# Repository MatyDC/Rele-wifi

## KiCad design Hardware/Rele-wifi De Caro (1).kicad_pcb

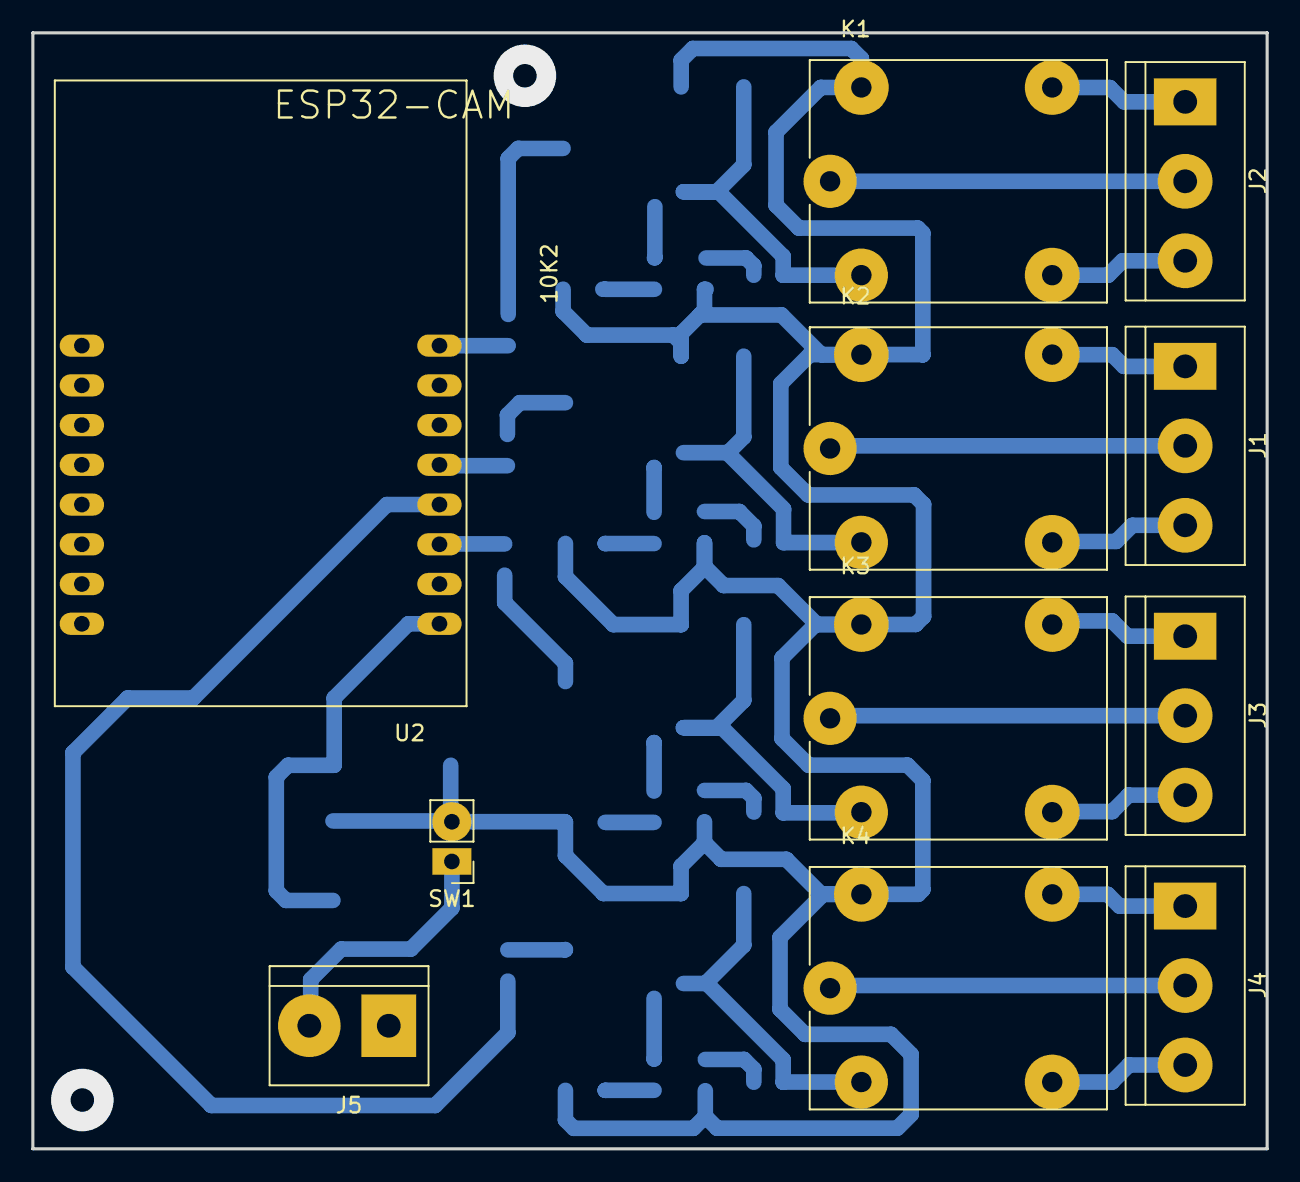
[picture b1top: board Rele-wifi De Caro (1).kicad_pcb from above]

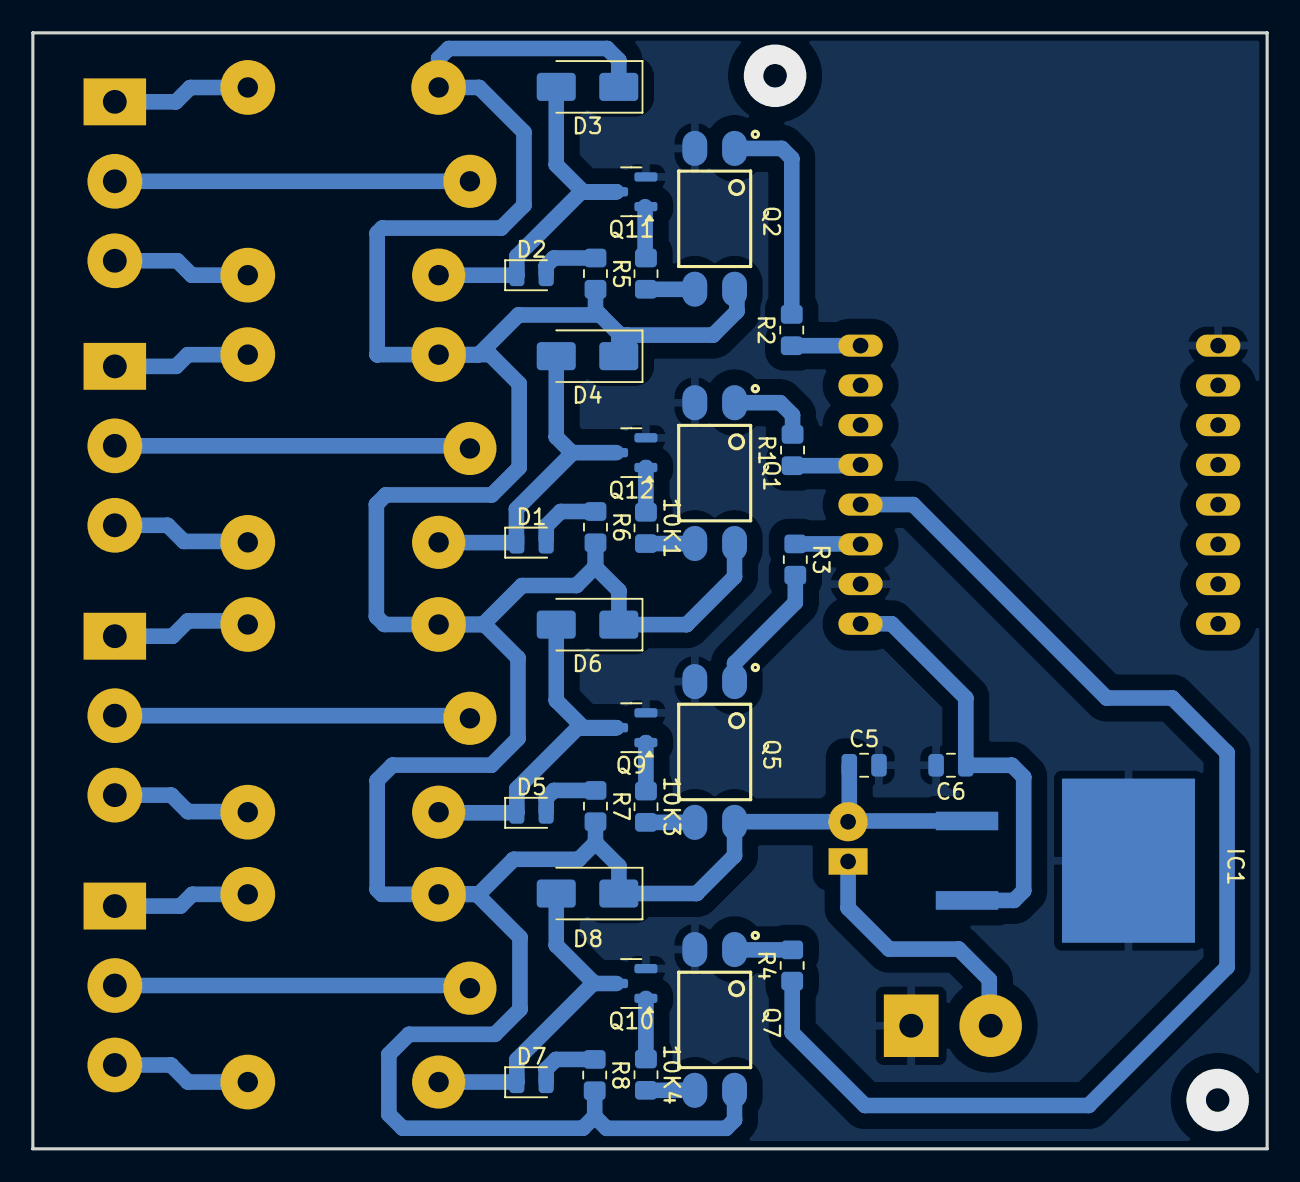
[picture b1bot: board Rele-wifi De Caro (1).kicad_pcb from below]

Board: 2 copper layers, 78.9 x 71.3 mm, 42 parts (31 on the bottom side), 40 nets.

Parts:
10K1, 10K2, 10K3, 10K4: R; R_0805_2012Metric_Pad1.20x1.40mm_HandSolder
C5, C6: 0.1uF; C_0805_2012Metric
D1, D2, D5, D7: LED; LED_0805_2012Metric
D3, D4, D6, D8: D; D_SMA
IC1: MC7805CD2TG
J1, J2, J3, J4: Screw_Terminal_01x03; TerminalBlock_bornier-3_P5.08mm
J5: Screw_Terminal_01x02; TerminalBlock_bornier-2_P5.08mm
K1, K2, K3, K4: PR13-5V-450-1C; RELAY_PR13-5V-450-1C
Q1, Q2, Q5, Q7: PC817-B; SOT254P1025X400-4N
Q9, Q10, Q11, Q12: BC847; SOT-23
R1, R2, R3, R4: 220; R_0805_2012Metric_Pad1.20x1.40mm_HandSolder
R5, R6, R7, R8: 680; R_0805_2012Metric_Pad1.20x1.40mm_HandSolder
SW1: SW_DPST_x2; PinHeader_1x02_P2.54mm_Vertical
U2: ESP32-CAM

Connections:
GND: C5.2, C6.2, IC1.P$1 (GND), J5.1, Q1.2, Q2.2, Q5.2, Q7.2, Q9.2 (E), Q10.2 (E), Q11.2 (E), Q12.2 (E), U2.P$2 (GND), U2.P$9 (.GND)
GPIO 4: R2.1, U2.P$8 (IO4)
GPIO 12: R3.1, U2.P$3 (IO12)
GPIO 13: R4.1, U2.P$4 (IO13)
GPIO 15: R1.1, U2.P$5 (IO15)
unnamed: 10K1.2, Q1.3
unnamed: 10K2.2, Q2.3
unnamed: 10K3.2, Q5.3
unnamed: 10K4.2, Q7.3
unnamed: D1.2 (A), R6.1
unnamed: D1.1 (K), D4.2 (A), K2.A2, Q12.3 (C)
unnamed: D2.2 (A), R5.1
unnamed: D2.1 (K), D3.2 (A), K1.A2, Q11.3 (C)
unnamed: D5.2 (A), R7.1
unnamed: D5.1 (K), D6.2 (A), K3.A2, Q9.3 (C)
unnamed: D7.2 (A), R8.1
unnamed: D7.1 (K), D8.2 (A), K4.A2, Q10.3 (C)
unnamed: C6.1, IC1.P$3 (VOUT), U2.P$1 (5V)
unnamed: J1.1, K2.NC
unnamed: J1.2, K2.COM
unnamed: J1.3, K2.NO
unnamed: J2.1, K1.NC
unnamed: J2.2, K1.COM
unnamed: J2.3, K1.NO
unnamed: J3.1, K3.NC
unnamed: J3.2, K3.COM
unnamed: J3.3, K3.NO
unnamed: J4.1, K4.NC
unnamed: J4.2, K4.COM
unnamed: J4.3, K4.NO
unnamed: J5.2, SW1.1 (A)
unnamed: Q1.1, R1.2
unnamed: Q2.1, R2.2
unnamed: Q5.1, R3.2
unnamed: Q7.1, R4.2
unnamed: 10K3.1, Q9.1 (B)
unnamed: 10K4.1, Q10.1 (B)
unnamed: 10K2.1, Q11.1 (B)
unnamed: 10K1.1, Q12.1 (B)
VCC: C5.1, D3.1 (K), D4.1 (K), D6.1 (K), D8.1 (K), IC1.P$2 (VIN), K1.A1, K2.A1, K3.A1, K4.A1, Q1.4, Q2.4, Q5.4, Q7.4, R5.2, R6.2, R7.2, R8.2, SW1.2 (B)

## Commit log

2025-05-07 Proyecto rele wifi kicad
2025-05-07 Agregue simbolos y huellas
2025-05-13 Avance de esquematico
2025-05-13 Agregue huella de relay
2025-05-24 Avance pcb
2025-06-13 PCB casi terminado
2025-06-13 PCB terminado
2025-06-13 Add files via upload
    PCB terminado
2025-06-18 PCB terminado y prolijo
2025-06-18 PCB terminado 2.0
